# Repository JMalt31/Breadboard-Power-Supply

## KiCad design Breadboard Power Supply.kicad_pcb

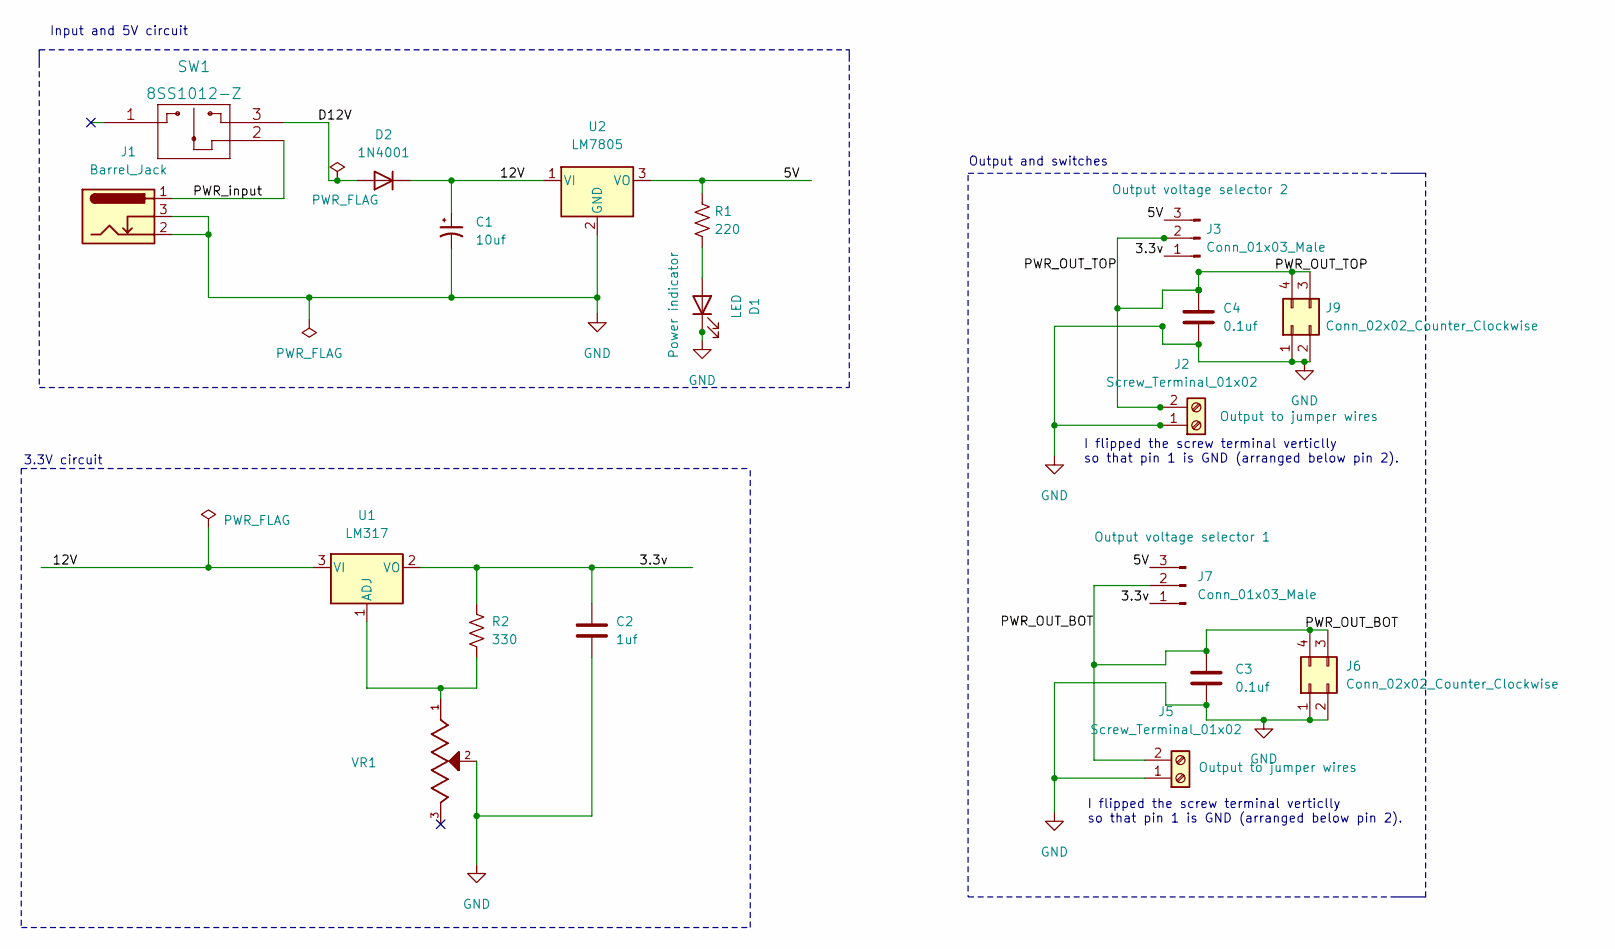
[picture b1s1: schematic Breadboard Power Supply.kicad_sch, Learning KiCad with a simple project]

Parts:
C1: 10uf; CP_Radial_D5.0mm_P2.50mm
C2: 1uf; C_Disc_D3.0mm_W1.6mm_P2.50mm
C3, C4: 0.1uf; C_Disc_D3.0mm_W1.6mm_P2.50mm
D1: LED; LED_D5.0mm
D2: 1N4001; D_DO-41_SOD81_P10.16mm_Horizontal
J1: Barrel_Jack; BarrelJack_Horizontal
J2, J5: Screw_Terminal_01x02; TerminalBlock_bornier-2_P5.08mm
J3, J7: Conn_01x03_Male; PinHeader_1x03_P2.54mm_Vertical
J6, J9: Conn_02x02_Counter_Clockwise; PinHeader_2x02_P2.54mm_Vertical
R1: 220; R_Axial_DIN0207_L6.3mm_D2.5mm_P10.16mm_Horizontal
R2: 330; R_Axial_DIN0207_L6.3mm_D2.5mm_P10.16mm_Horizontal
SW1: 8SS1012-Z; 8SS1012_NDC
U1: LM317; TO-220-3_Vertical
U2: LM7805; TO-220-3_Vertical
VR1: 3296W-1-102; TRIM_3296W-1-102; PARTREV 05/16

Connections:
/3.3v: C2.1, J3.1, J7.1, R2.2, U1.2 (VO)
/5V: J3.3, J7.3, R1.1, U2.3 (VO)
/12V: C1.1, D2.1 (K), U1.3 (VI), U2.1 (VI)
/D12V: D2.2 (A), SW1.3
/PWR_OUT_BOT: C3.1, J5.2, J6.3, J6.4, J7.2
/PWR_OUT_TOP: C4.2, J2.2, J3.2, J9.3, J9.4
/PWR_input: J1.1, SW1.2
GND: C1.2, C2.2, C3.2, C4.1, D1.1 (K), J1.2, J1.3, J2.1, J5.1, J6.1, J6.2, J9.1, J9.2, U2.2 (GND), VR1.2
unnamed: D1.2 (A), R1.2
unnamed: R2.1, U1.1 (ADJ), VR1.1

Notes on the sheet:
Output and switches
I flipped the screw terminal verticlly so that pin 1 is GND (arranged below pin 2).
Input and 5V circuit
3.3V circuit

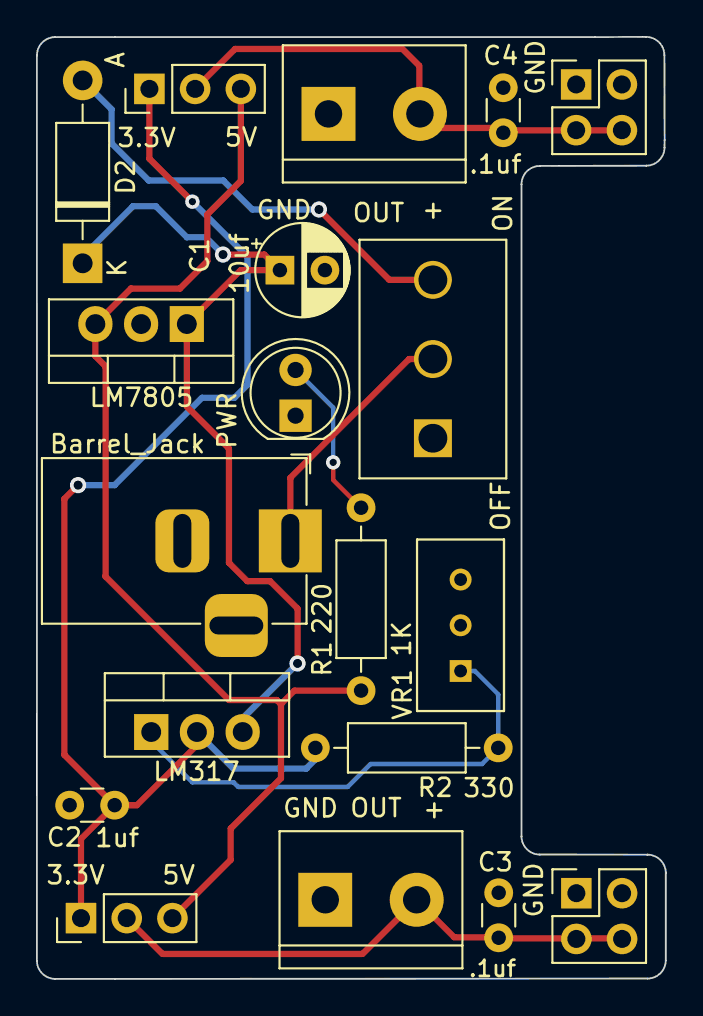
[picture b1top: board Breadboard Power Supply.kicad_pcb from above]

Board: 2 copper layers, 34.9 x 52.3 mm, 19 parts (0 on the bottom side), 10 nets.

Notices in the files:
parts and their libraries:
Copyright 2021 Accelerated Designs. All rights reserved.
